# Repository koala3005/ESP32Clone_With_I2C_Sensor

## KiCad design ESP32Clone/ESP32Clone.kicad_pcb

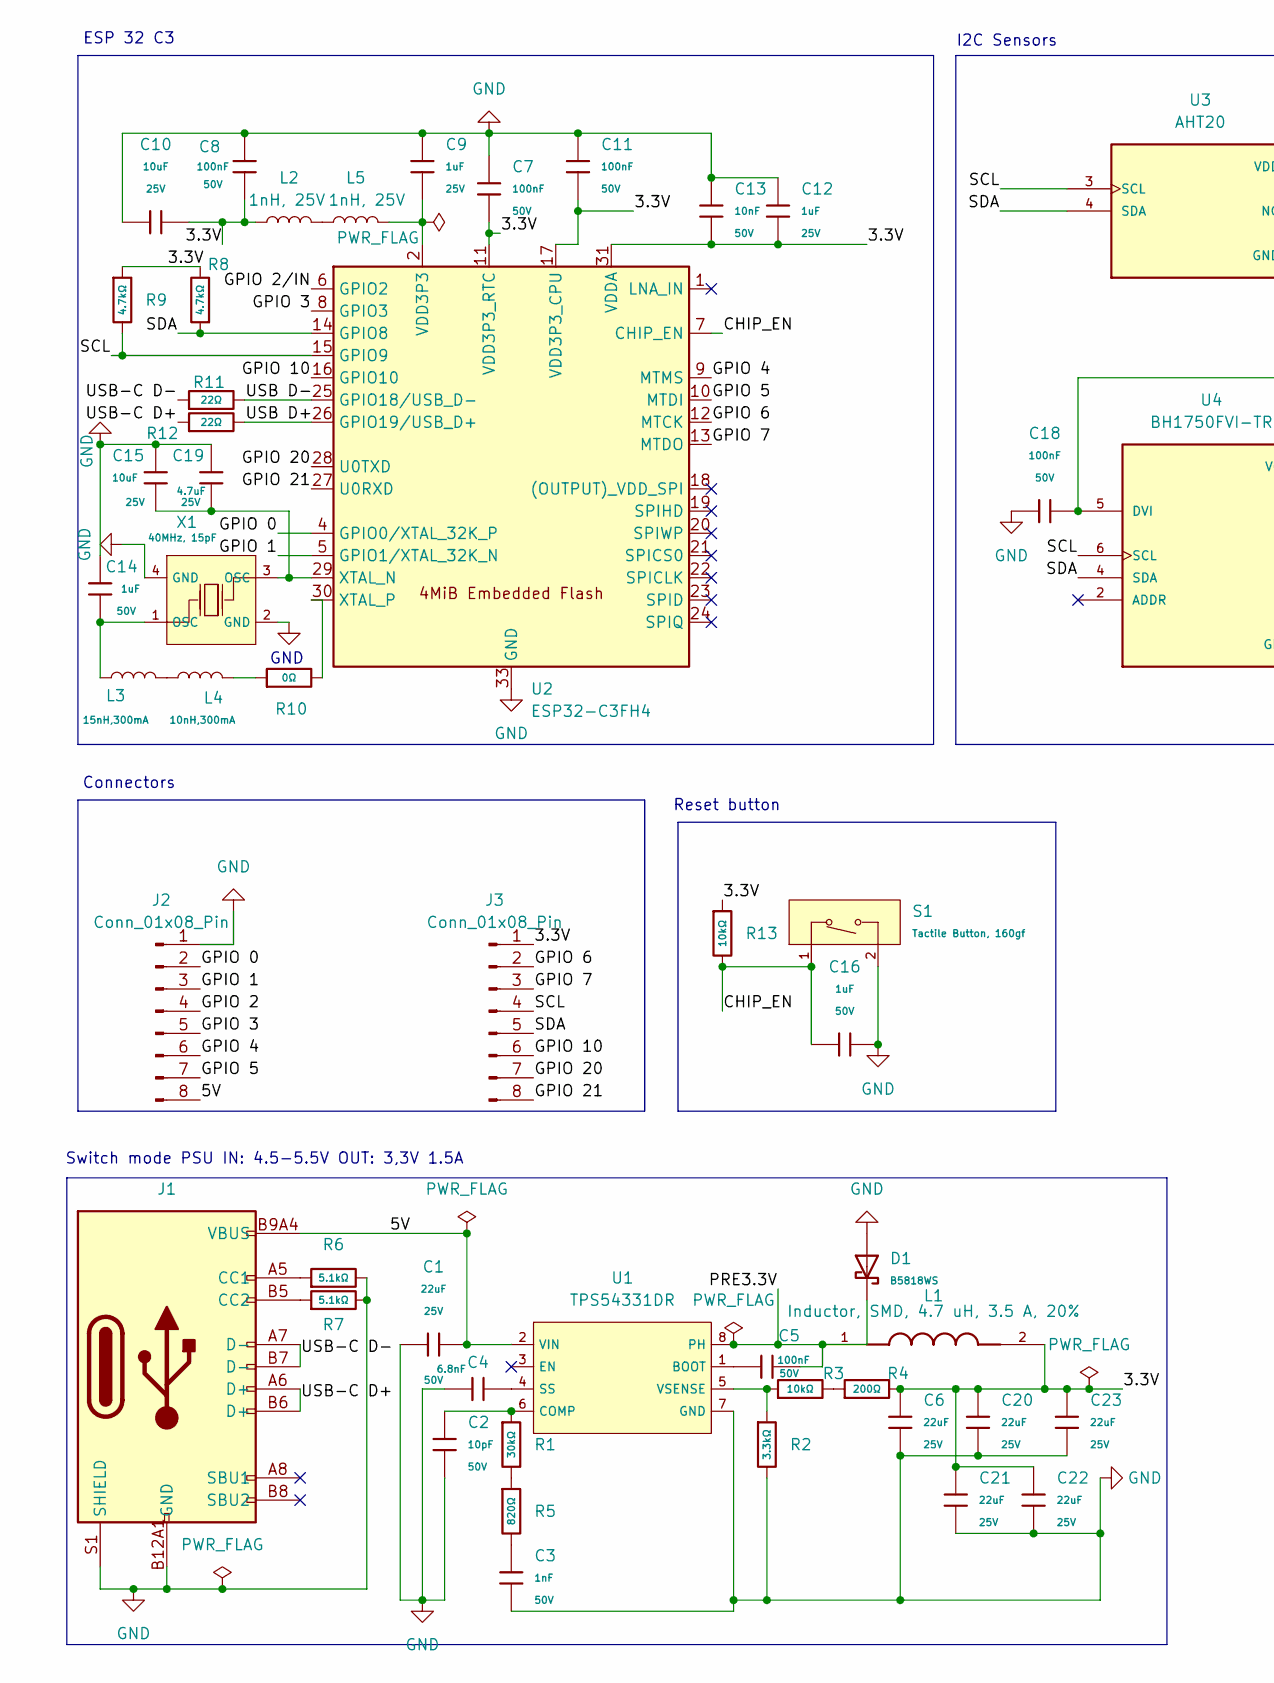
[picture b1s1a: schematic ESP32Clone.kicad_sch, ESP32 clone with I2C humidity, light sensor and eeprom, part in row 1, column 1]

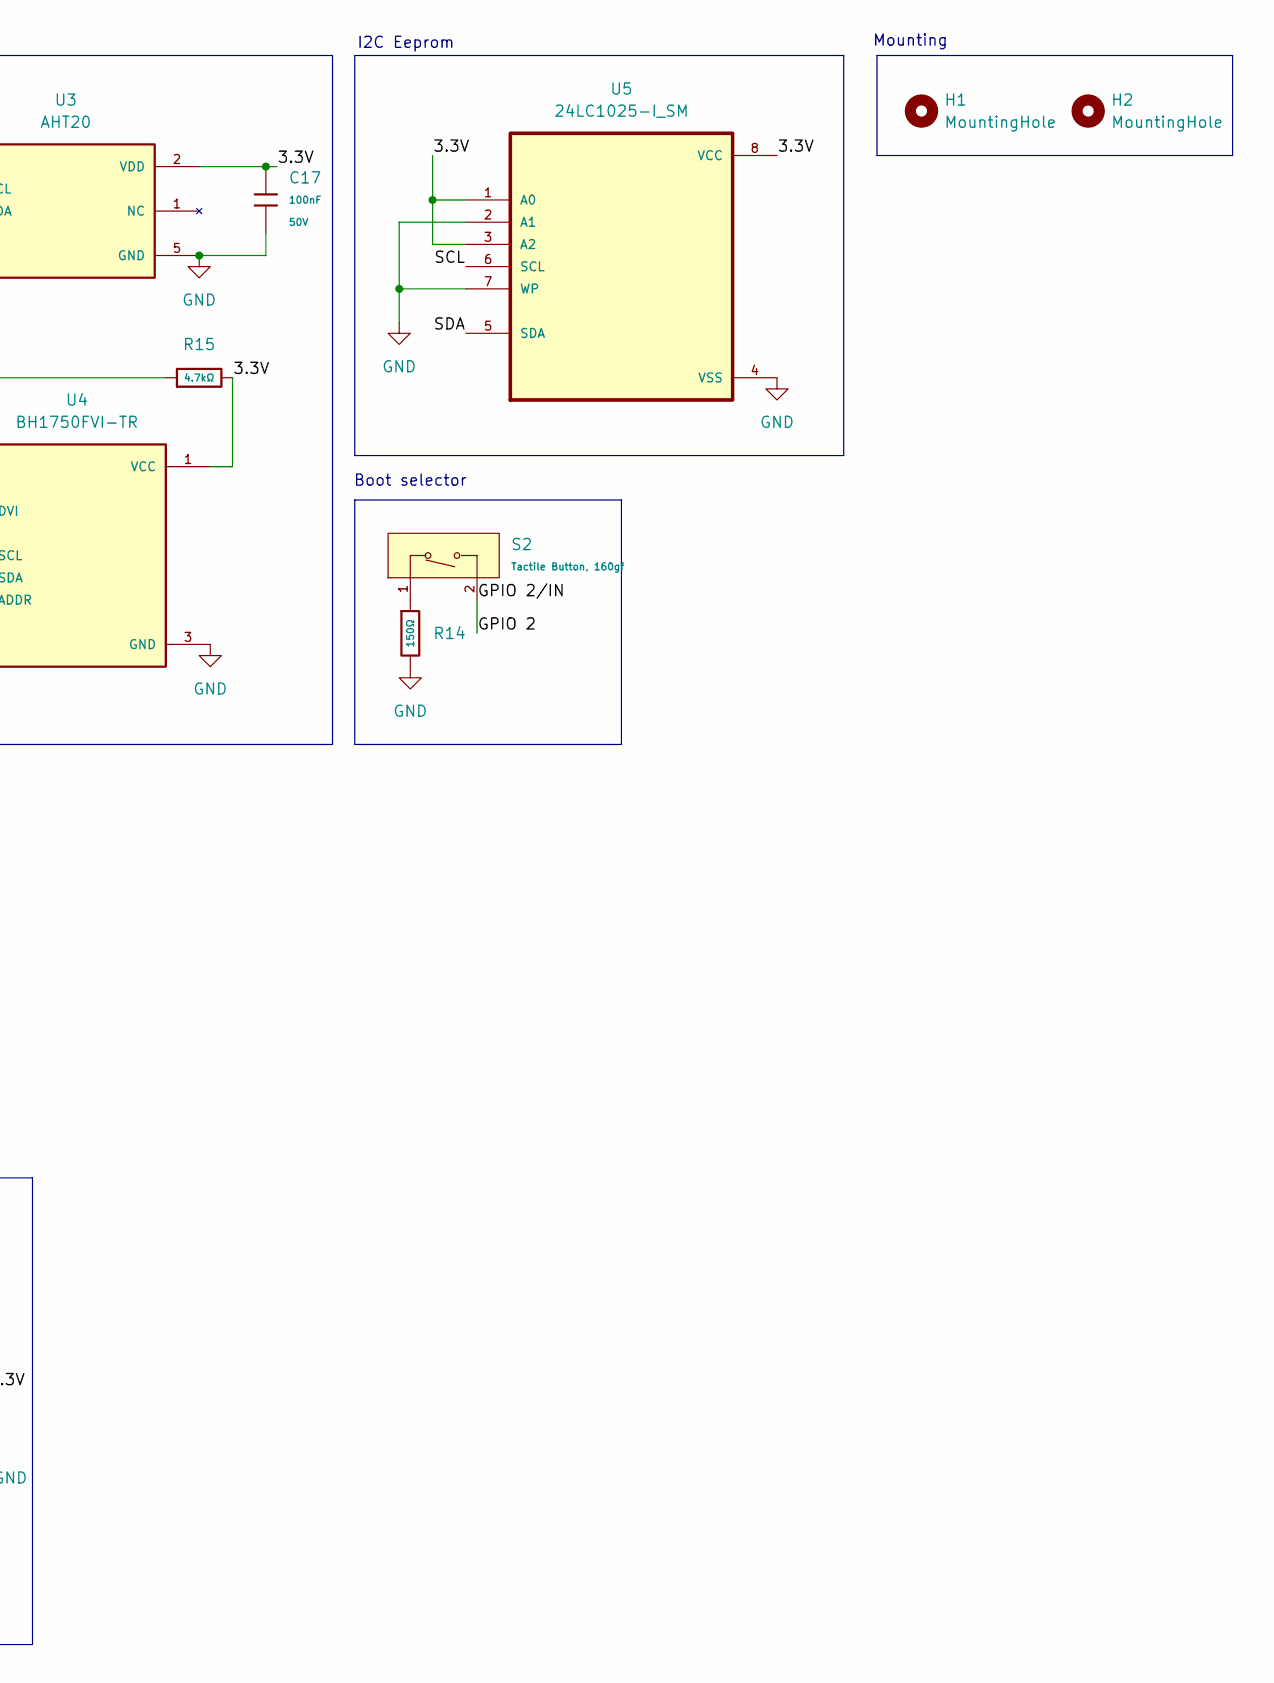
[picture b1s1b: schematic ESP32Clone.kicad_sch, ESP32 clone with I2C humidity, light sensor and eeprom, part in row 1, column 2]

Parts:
C1, C6, C20, C21, C22, C23: 22uF; C_0805; Voltage Rated 25V; Tolerance ±20%; Part CL21A226MAQNNNE; LCSC C45783
C2: 10pF; C_0402; Voltage Rated 50V; Tolerance ±5%; Part CL05C100JB5NNNC; LCSC C32949
C3: 1nF; C_0402; Voltage Rated 50V; Tolerance ±10%; Part 0402B102K500NT; LCSC C1523
C4: 6.8nF; C_0402; Voltage Rated 50V; Tolerance ±10%; Part 0402B682K500NT; LCSC C1542
C5, C7, C8, C11, C17, C18: 100nF; C_0603; Voltage Rated 50V; Tolerance ±10%; Part CC0603KRX7R9BB104; LCSC C14663
C9, C12: 1uF; C_0402; Voltage Rated 25V; Tolerance ±10%; Part CL05A105KA5NQNC; LCSC C52923
C10, C15: 10uF; C_0603; Voltage Rated 25V; Tolerance ±20%; Part CL10A106MA8NRNC; LCSC C96446
C13: 10nF; C_0402; Voltage Rated 50V; Tolerance ±10%; Part CL05B103KB5NNNC; LCSC C15195
C14, C16: 1uF; C_0603; Voltage Rated 50V; Tolerance ±10%; Part CL10A105KB8NNNC; LCSC C15849
C19: 4.7uF; C_0805; Voltage Rated 25V; Tolerance ±10%; Part CL21A475KAQNNNE; LCSC C1779
D1: B5818WS; D_SOD-323; Forward Voltage (Vf@If) 550mV@1A; Reverse Voltage (Vr) 30V; Part B5818WS; LCSC C22466361
H1, H2: MountingHole; MountingHole_2.1mm
J1: Connector, USB-TYPE-C-16P; TYPE-C-SMD_HX-TYPE-C-16PIN; Part USB-TYPE-C-019; LCSC C2927039
J2, J3: Conn_01x08_Pin; PinHeader_1x08_P2.54mm_Vertical; Part CS-1109-1X8(L11.5)PA6T; LCSC C18213722
L1: Inductor, SMD, 4.7 uH, 3.5 A, 20%; IND_SRP4020TA-4R7M; Part SRP4020TA-4R7M; LCSC C2041623
L2, L5: 1nH, 25V; L_0603; Part VHF160808H1N0ST; LCSC C1027
L3: 15nH,300mA; L_0402; Tolerance ±5%; Part SDCL1005C15NJTDF; LCSC C27143
L4: 10nH,300mA; L_0402; Tolerance ±5%; Part SDCL1005C10NJTDF; LCSC C27147
R1: 30kΩ; R_0805; Overload Voltage (Max) 150V; Tolerance ±1%; Part 0805W8F3002T5E; LCSC C17621
R2: 3.3kΩ; R_0402; Overload Voltage (Max) 50V; Tolerance ±1%; Part 0402WGF3301TCE; LCSC C25890
R3: 10kΩ; R_0402; Overload Voltage (Max) 50V; Tolerance ±1%; Part 0402WGF1002TCE; LCSC C25744
R4: 200Ω; R_0402; Overload Voltage (Max) 50V; Tolerance ±1%; Part 0402WGF2000TCE; LCSC C25087
R5: 820Ω; R_0805; Overload Voltage (Max) 150V; Tolerance ±1%; Part 0805W8F8200T5E; LCSC C17837
R6, R7: 5.1kΩ; R_0805; Overload Voltage (Max) 150V; Tolerance ±1%; Part 0805W8F5101T5E; LCSC C27834
R8, R9, R15: 4.7kΩ; R_0805; Overload Voltage (Max) 150V; Tolerance ±1%; Part 0805W8F4701T5E; LCSC C17673
R10: 0Ω; R_0805; Overload Voltage (Max) 150V; Tolerance ±1%; Part 0805W8F0000T5E; LCSC C17477
R11, R12: 22Ω; R_0805; Overload Voltage (Max) 150V; Tolerance ±1%; Part 0805W8F220JT5E; LCSC C17561
R13: 10kΩ; R_0603; Overload Voltage (Max) 75V; Tolerance ±1%; Part 0603WAF1002T5E; LCSC C25804
R14: 150Ω; R_0805; Overload Voltage (Max) 150V; Tolerance ±1%; Part 0805W8F1500T5E; LCSC C17471
S1, S2: Tactile Button, 160gf; SW_TS-1088-AR02016; Voltage Rating (Dc) 12V; Part TS-1088-AR02016; LCSC C720477
U1: TPS54331DR; SOIC-8_L5.0-W4.0-P1.27-LS6.0-BL; Output Voltage 0.8V~25V; Input Voltage 3.5V~28V; Part TPS54331DR; LCSC C9865
U2: ESP32-C3FH4; QFN-32-1EP_5x5mm_P0.5mm_EP3.7x3.7mm_ThermalVias; Part ESP32-C3FH4; LCSC C2858491
U3: AHT20; PSON100P300X300X110-6N; PARTREV V1.0; LCSC C2757850
U4: BH1750FVI-TR; XDCR_BH1750FVI-TR; PARTREV D; LCSC C78960
U5: 24LC1025-I_SM; SOIC127P794X202-8N; Part 24LC1025-I/SM; DigiKey_Part_Number 24LC1025-I/SM-ND
X1: 40MHz, 15pF; OSC-SMD_4P-L3.2-W2.5-BL_SIT8008BI; PartID X322540MPB4SI; LCSC C9010

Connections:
/3.3V: C6.1, C7.2, C8.2, C10.2, C11.2, C12.1, C13.2, C17.1, C20.1, C21.1, C22.1, C23.1, J3.1, L1.2, L2.1, R4.2, R8.2, R9.1, R13.1, R15.2, U2.11 (VDD3P3_RTC), U2.17 (VDD3P3_CPU), U2.31 (VDDA), U2.32 (VDDA), U3.2 (VDD), U4.1 (VCC), U5.1 (A0), U5.3 (A2), U5.8 (VCC)
/5V: C1.2, J1.A9B4 (VBUS), J1.B9A4 (VBUS), J2.8, U1.2 (VIN)
/CHIP_EN: C16.1, R13.2, S1.1 (A), U2.7 (CHIP_EN)
/GPIO 0: J2.2, U2.4 (GPIO0/XTAL_32K_P)
/GPIO 1: J2.3, U2.5 (GPIO1/XTAL_32K_N)
/GPIO 2: J2.4, S2.2 (B), U2.6 (GPIO2)
/GPIO 3: J2.5, U2.8 (GPIO3)
/GPIO 4: J2.6, U2.9 (MTMS)
/GPIO 5: J2.7, U2.10 (MTDI)
/GPIO 6: J3.2, U2.12 (MTCK)
/GPIO 7: J3.3, U2.13 (MTDO)
/GPIO 10: J3.6, U2.16 (GPIO10)
/GPIO 20: J3.7, U2.28 (U0TXD)
/GPIO 21: J3.8, U2.27 (U0RXD)
/PRE3.3V: C5.1, D1.1, L1.1, U1.8 (PH)
/SCL: J3.4, R9.2, U2.15 (GPIO9), U3.3 (SCL), U4.6 (SCL), U5.6 (SCL)
/SDA: J3.5, R8.1, U2.14 (GPIO8), U3.4 (SDA), U4.4 (SDA), U5.5 (SDA)
/USB D+: R12.2, U2.26 (GPIO19/USB_D+)
/USB D-: R11.2, U2.25 (GPIO18/USB_D-)
/USB-C D+: J1.A6 (D+), J1.B6 (D+), R12.1
/USB-C D-: J1.A7 (D-), J1.B7 (D-), R11.1
GND: C1.1, C2.2, C3.1, C4.1, C6.2, C7.1, C8.1, C9.1, C10.1, C11.1, C12.2, C13.1, C14.1, C15.1, C16.2, C17.2, C18.1, C19.1, C20.2, C21.2, C22.2, C23.2, D1.2, J1.A12B1 (GND), J1.B12A1 (GND), J1.S1 (SHIELD), J2.1, R2.2, R6.2, R7.2, R14.2, S1.2 (B), U1.7 (GND), U2.33 (GND), U3.5 (GND), U4.3 (GND), U5.2 (A1), U5.4 (VSS), U5.7 (WP), X1.2 (GND), X1.4 (GND)
unnamed: C3.2, R5.2
unnamed: C9.2, L5.2, U2.2 (VDD3P3), U2.3 (VDD3P3)
unnamed: C14.2, L3.1, X1.1 (OSC)
unnamed: J1.A5 (CC1), R6.1
unnamed: J1.B5 (CC2), R7.1
unnamed: L2.2, L5.1
unnamed: L3.2, L4.1
unnamed: L4.2, R10.1
unnamed: R1.2, R5.1
unnamed: R3.2, R4.1
unnamed: R14.1, S2.1 (A)
unnamed: C5.2, U1.1 (BOOT)
unnamed: C2.1, R1.1, U1.6 (COMP)
unnamed: C4.2, U1.4 (SS)
unnamed: R2.1, R3.1, U1.5 (VSENSE)
unnamed: C15.2, C19.2, U2.29 (XTAL_N), X1.3 (OSC)
unnamed: R10.2, U2.30 (XTAL_P)
unnamed: C18.2, R15.1, U4.5 (DVI)

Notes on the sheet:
Mounting
Switch mode PSU IN: 4.5-5.5V OUT: 3,3V 1.5A
I2C Eeprom
I2C Sensors
Reset button
GND
ESP 32 C3
Boot selector
Connectors

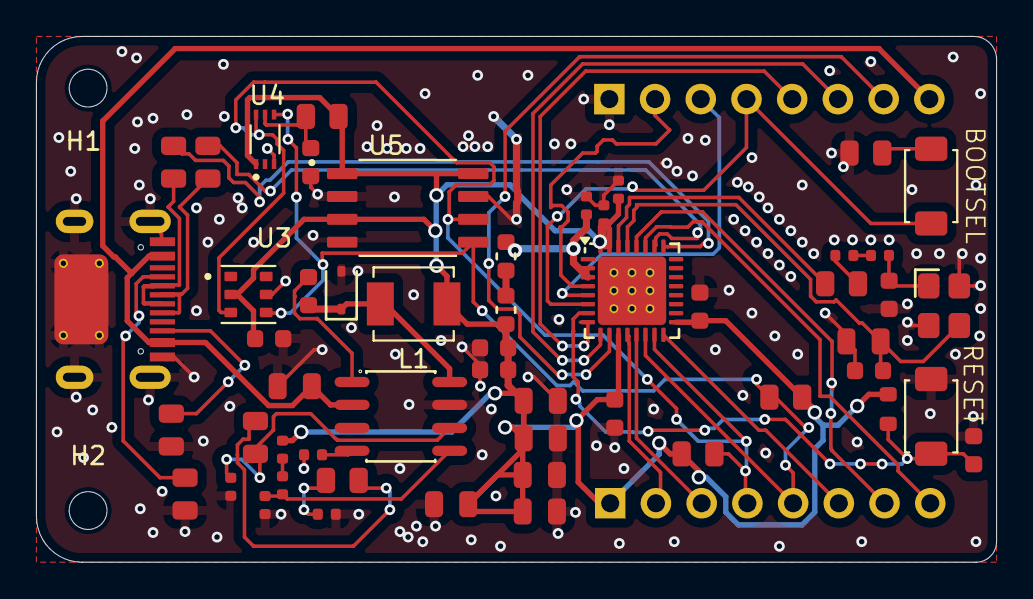
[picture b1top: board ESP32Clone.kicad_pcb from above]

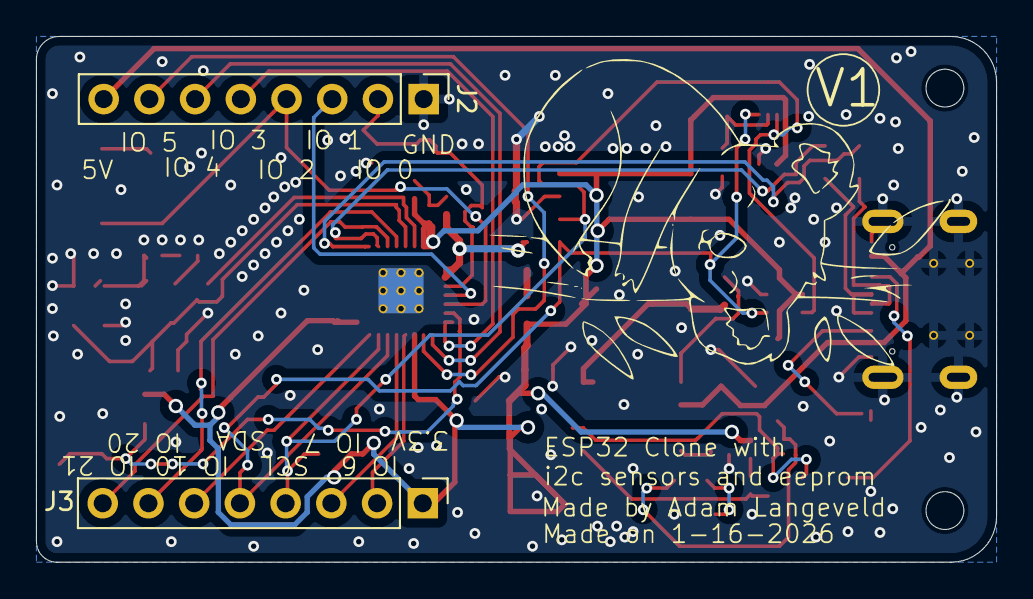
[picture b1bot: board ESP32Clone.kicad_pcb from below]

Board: 2 copper layers, 53.3 x 29.2 mm, 57 parts (2 on the bottom side), 40 nets.

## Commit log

2025-12-17 PSU and USB-C port added
2025-12-17 connected configuration pins
2025-12-17 ESP 32 added
2025-12-29 File update
2025-12-29 Finished esp32
2025-12-29 Added connecter and reset switch
2025-12-29 Further work on connectors
2026-01-01 Added IC2 devices
2026-01-01 Changed text color
2026-01-01 Added footprints
2026-01-01 Resolved ERC issue's and filled in sheet info
    Warning's remaining:
    Current configuration does not include symbol library 'Connector'.
    Is just a warning because of the configuration i have where only custom and JLCPCB libraries are on
    Pin with no connection type is connected.
    This pin is connected to a no connect flag, feel like that should'nt give a warning
2026-01-01 Autosave and backup
2026-01-05 Added more IO and boot selector
2026-01-05 The thing i said before forgot to save
2026-01-05 Fixed footprint
2026-01-05 Replaced capictor
2026-01-05 PCB started
2026-01-06 Done DRC
    only has a few library issue's left
2026-01-08 Autosave Things
2026-01-08 added silkscreen
2026-01-08 added funny koala
2026-01-12 cleaned up files
2026-01-12 moved footprint files into the git directory
2026-01-12 Added last few 3D files
2026-01-14 Added mounting holes and fixed erc warnings
    ERC warning remaining:
    Pin no connection type is connected, its connected to a no connect flag somehow thats a warning.
    Both Gpio 2 GPIO 2/IN are connected to the same item. this is correct it has to do with the boot select
2026-01-14 Fixed DRC
    DRC remianing:
    3x Koala figure silkscreen clipped by something,
    the koala is giant and doesnt give importent information so its fine
2026-01-14 forgot to save
2026-01-14 fixed long vsense wire
2026-01-16 removed a few islands and generated bom
2026-01-16 generated bom correctly
